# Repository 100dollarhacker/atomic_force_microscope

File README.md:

This repository holds the files for creating simple diy atomic force microscope.

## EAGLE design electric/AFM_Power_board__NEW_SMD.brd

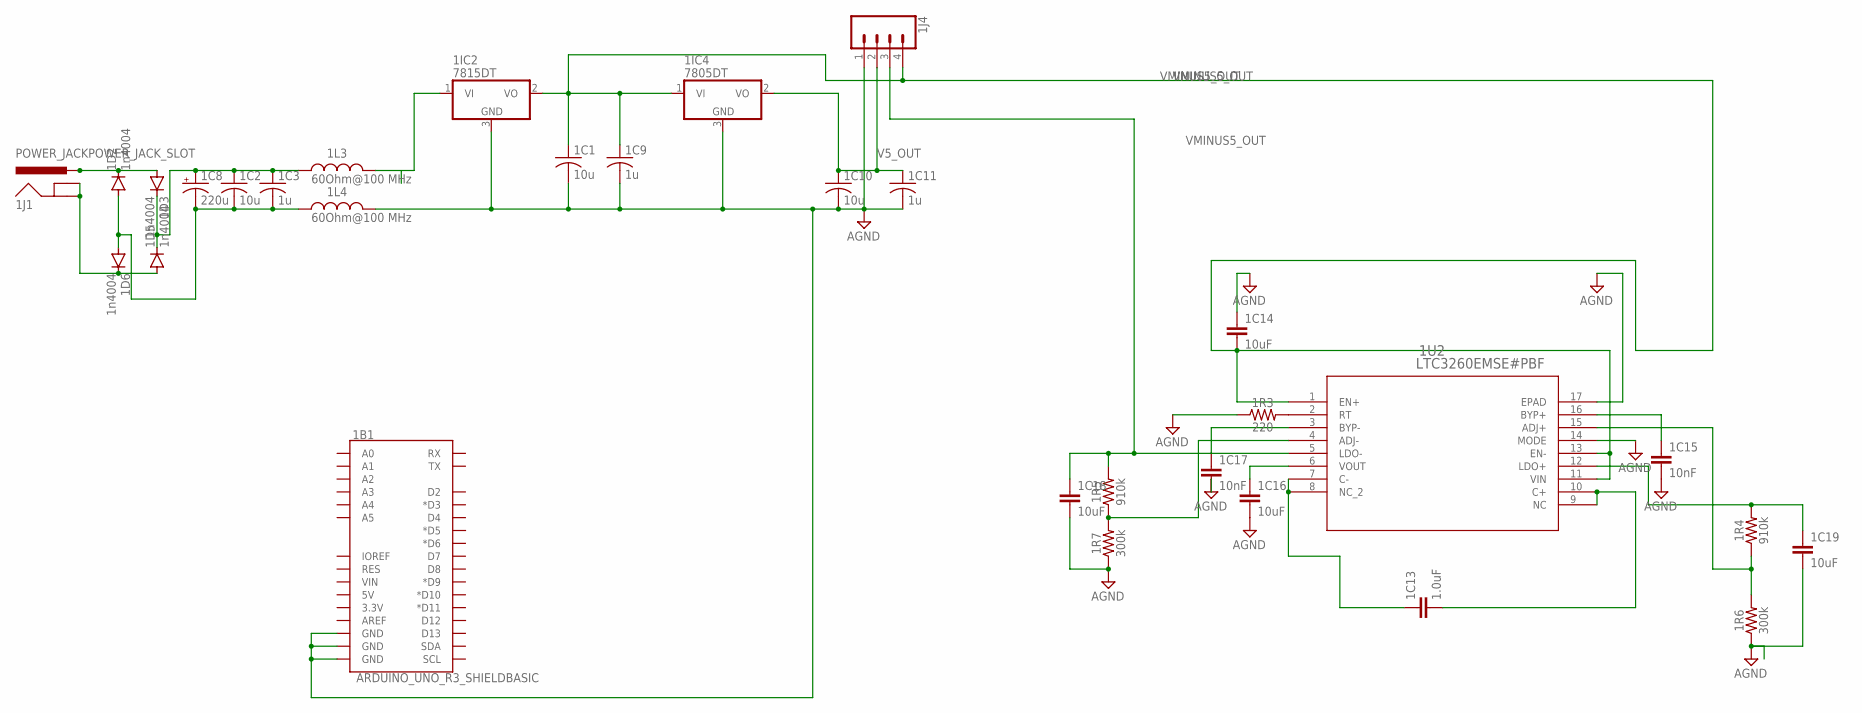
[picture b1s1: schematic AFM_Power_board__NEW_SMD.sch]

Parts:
1B1: ARDUINO_UNO_R3_SHIELDBASIC; UNO_R3_SHIELD
1C1, 1C10: 10u; C0603
1C2: 10u; C1210
1C3: 1u; C1210
1C8: 220u; 140CLH-1014
1C9, 1C11: 1u; C0603
1C13: 1.0uF; 0805
1C14, 1C16, 1C18, 1C19: 10uF; 0805
1C15, 1C17: 10nF; 0603
1D2, 1D3, 1D5, 1D6: 1n4004; SOD123
1IC2: 7815DT; TO252
1IC4: 7805DT; TO252
1J1: POWER_JACKPOWER_JACK_SLOT; POWER_JACK_PTH_SLOT
1J4: CONN_04LONGPADS; 1X04_LONGPADS
1L3, 1L4: 60Ohm@100 MHz; WE-CBF_0603_W2.2
1R3: 220; 0603
1R4, 1R5: 910k; 0603
1R6, 1R7: 300k; 0603
1U2: LTC3260EMSE#PBF; MSOP-16_MSE

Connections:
AGND: 1B1.GND@0 (GND), 1B1.GND@1 (GND), 1B1.GND@2 (GND), 1C1.2, 1C9.2, 1C10.2, 1C11.2, 1C14.1, 1C15.2, 1C16.2, 1C17.2, 1C18.2, 1C19.2, 1IC2.3 (GND), 1IC4.3 (GND), 1J4.1, 1L4.2, 1R3.1, 1R6.1, 1R7.1, 1U2.14 (MODE), 1U2.17 (EPAD)
GROUND: 1C2.2, 1C3.2, 1C8.-, 1D2.A, 1D6.A, 1L4.1
LDO+: 1C19.1, 1R4.2, 1U2.12 (LDO+)
unnamed: 1D5.A, 1D6.C, 1J1.GND, 1J1.GNDBREAK
unnamed: 1IC2.1 (VI), 1L3.2
unnamed: 1C13.1, 1U2.7 (C-), 1U2.8 (NC_2)
unnamed: 1C13.2, 1U2.9 (NC), 1U2.10 (C+)
unnamed: 1C2.1, 1C3.1, 1C8.+, 1D3.C, 1D5.C, 1L3.1
unnamed: 1C17.1, 1U2.3 (BYP-)
unnamed: 1C15.1, 1U2.16 (BYP+)
unnamed: 1C16.1, 1U2.6 (VOUT)
unnamed: 1R3.2, 1U2.2 (RT)
unnamed: 1R5.1, 1R7.2, 1U2.4 (ADJ-)
unnamed: 1R4.1, 1R6.2, 1U2.15 (ADJ+)
POWERP: 1D2.C, 1D3.A, 1J1.PWR
V5_OUT: 1C10.1, 1C11.1, 1IC4.2 (VO), 1J4.2
V15+: 1C1.1, 1C9.1, 1C14.2, 1IC2.2 (VO), 1IC4.1 (VI), 1J4.4, 1U2.1 (EN+), 1U2.11 (VIN), 1U2.13 (EN-)
VMINUS5_OUT: 1C18.1, 1J4.3, 1R5.2, 1U2.5 (LDO-)

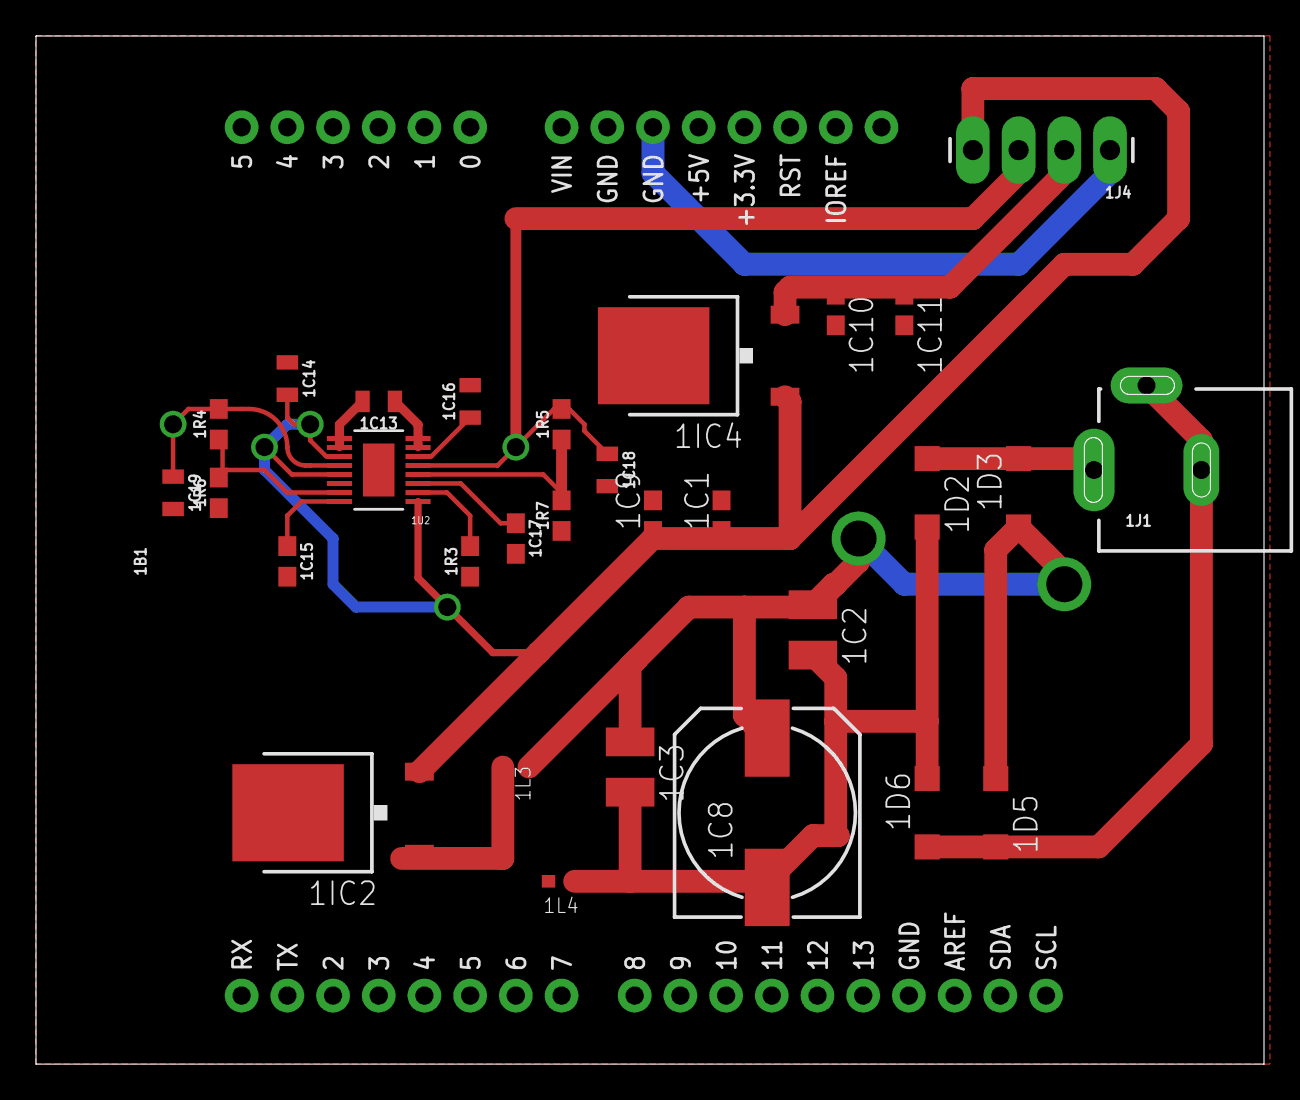
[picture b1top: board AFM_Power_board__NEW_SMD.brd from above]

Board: 2 copper layers, 68.2 x 57.1 mm, 31 parts (0 on the bottom side), 18 nets.

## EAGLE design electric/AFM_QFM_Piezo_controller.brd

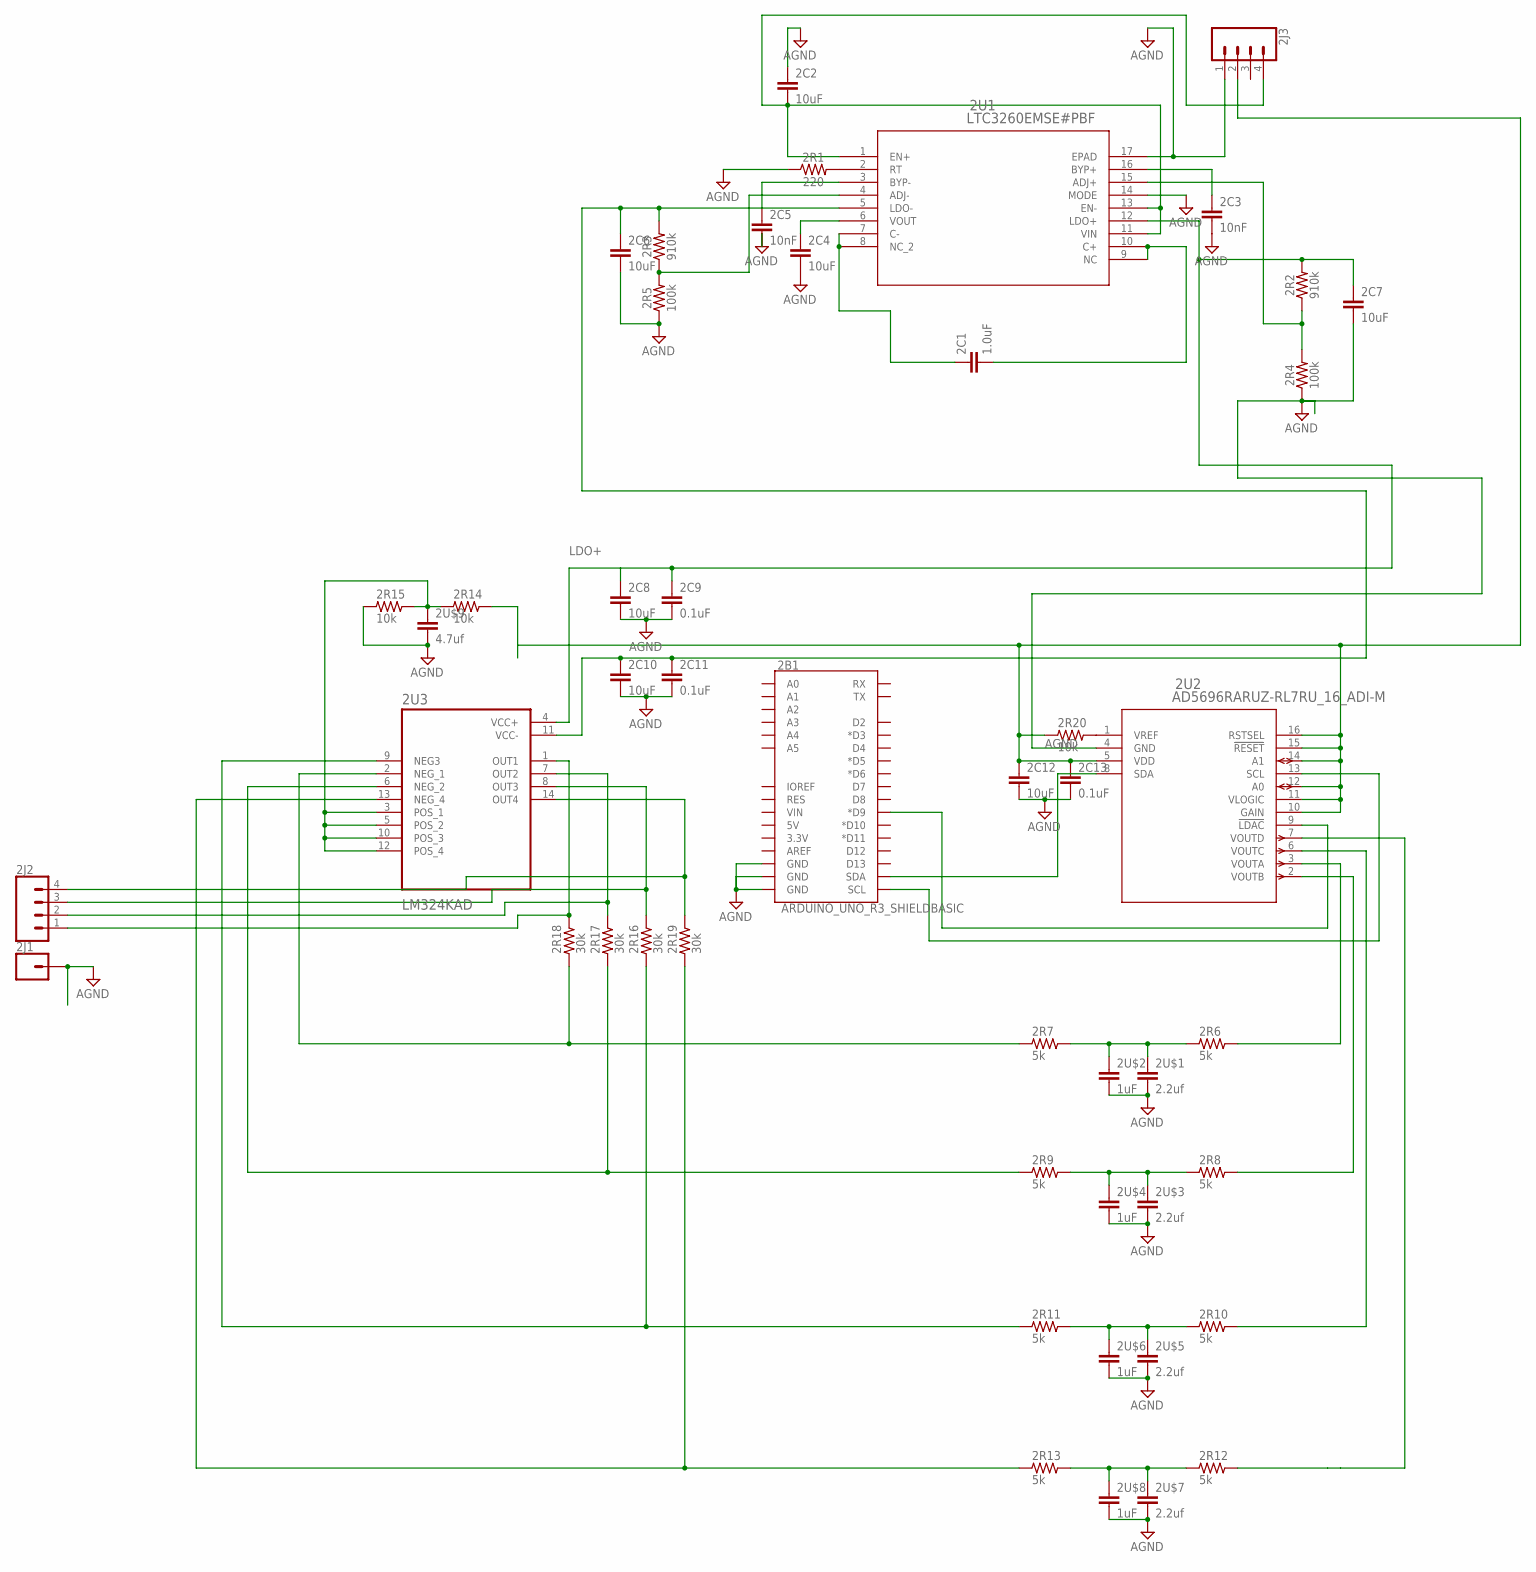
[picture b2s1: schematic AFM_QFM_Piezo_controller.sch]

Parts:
2B1: ARDUINO_UNO_R3_SHIELDBASIC; UNO_R3_SHIELD
2C1: 1.0uF; 0805
2C2, 2C4, 2C6, 2C7, 2C8, 2C10, 2C12: 10uF; 0805
2C3, 2C5: 10nF; 0603
2C9, 2C11, 2C13: 0.1uF; C0805
2J1: CONN_01PTH_LONGPAD; 1X01_LONGPAD
2J2, 2J3: CONN_04LONGPADS; 1X04_LONGPADS
2R1: 220; 0603
2R2, 2R3: 910k; 0603
2R4, 2R5: 100k; 0603
2R6, 2R7, 2R8, 2R9, 2R10, 2R11, 2R12, 2R13: 5k; RC-MASTER-SMD_R0603MP
2R14, 2R15, 2R20: 10k; RC-MASTER-SMD_R0603MP
2R16, 2R17, 2R18, 2R19: 30k; RC-MASTER-SMD_R0603MP
2U1: LTC3260EMSE#PBF; MSOP-16_MSE
2U2: AD5696RARUZ-RL7RU_16_ADI-M; RU_16_ADI-M
2U3: LM324KAD; SOIC127P600X175-14N
2U$1, 2U$3, 2U$5, 2U$7: 2.2uf; RESC0603_M
2U$2, 2U$4, 2U$6, 2U$8: 1uF; RESC0603_M
2U$9: 4.7uf; RESC0603_M

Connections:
AGND: 2B1.GND@0 (GND), 2B1.GND@1 (GND), 2B1.GND@2 (GND), 2C2.1, 2C3.2, 2C4.2, 2C5.2, 2C6.2, 2C7.2, 2C8.2, 2C9.2, 2C10.2, 2C11.2, 2C12.2, 2C13.2, 2J1.1, 2J3.1, 2R1.1, 2R4.1, 2R5.1, 2R15.1, 2U1.14 (MODE), 2U1.17 (EPAD), 2U2.4 (GND), 2U$1.2, 2U$2.2, 2U$3.2, 2U$4.2, 2U$5.2, 2U$6.2, 2U$7.2, 2U$8.2, 2U$9.2
LDAC: 2B1.D9 (*D9), 2U2.9 (!LDAC)
LDO+: 2C7.1, 2C8.1, 2C9.1, 2R2.2, 2U1.12 (LDO+), 2U3.4 (VCC+)
LDO-: 2C6.1, 2C10.1, 2C11.1, 2R3.2, 2U1.5 (LDO-), 2U3.11 (VCC-)
unnamed: 2C5.1, 2U1.3 (BYP-)
unnamed: 2R1.2, 2U1.2 (RT)
unnamed: 2C1.1, 2U1.7 (C-), 2U1.8 (NC_2)
unnamed: 2C1.2, 2U1.9 (NC), 2U1.10 (C+)
unnamed: 2C3.1, 2U1.16 (BYP+)
unnamed: 2C4.1, 2U1.6 (VOUT)
unnamed: 2R3.1, 2R5.2, 2U1.4 (ADJ-)
unnamed: 2R6.1, 2R7.2, 2U$1.1, 2U$2.1
unnamed: 2R2.1, 2R4.2, 2U1.15 (ADJ+)
unnamed: 2R7.1, 2R18.1, 2U3.2 (NEG_1)
unnamed: 2R8.1, 2R9.2, 2U$3.1, 2U$4.1
unnamed: 2R9.1, 2R17.1, 2U3.6 (NEG_2)
unnamed: 2R10.1, 2R11.2, 2U$5.1, 2U$6.1
unnamed: 2R11.1, 2R16.1, 2U3.9 (NEG3)
unnamed: 2R12.1, 2R13.2, 2U$7.1, 2U$8.1
unnamed: 2R13.1, 2R19.1, 2U3.13 (NEG_4)
unnamed: 2R20.2, 2U2.1 (VREF)
P_OUT1: 2J2.1, 2R18.2, 2U3.1 (OUT1)
P_OUT2: 2J2.2, 2R17.2, 2U3.7 (OUT2)
P_OUT3: 2J2.3, 2R16.2, 2U3.8 (OUT3)
P_OUT4: 2J2.4, 2R19.2, 2U3.14 (OUT4)
SCL: 2B1.SCL, 2U2.13 (SCL)
SDA: 2B1.SDA, 2U2.8 (SDA)
V15+: 2C2.2, 2J3.4, 2U1.1 (EN+), 2U1.11 (VIN), 2U1.13 (EN-)
VDD: 2C12.1, 2C13.1, 2J3.2, 2R14.2, 2R20.1, 2U2.5 (VDD), 2U2.10 (GAIN), 2U2.11 (VLOGIC), 2U2.12 (A0), 2U2.14 (A1), 2U2.15 (!RESET), 2U2.16 (RSTSEL)
VOUTA: 2R6.2, 2U2.3 (VOUTA)
VOUTB: 2R8.2, 2U2.2 (VOUTB)
VOUTC: 2R10.2, 2U2.6 (VOUTC)
VOUTD: 2R12.2, 2U2.7 (VOUTD)
V_REF: 2R14.1, 2R15.2, 2U3.3 (POS_1), 2U3.5 (POS_2), 2U3.10 (POS_3), 2U3.12 (POS_4), 2U$9.1

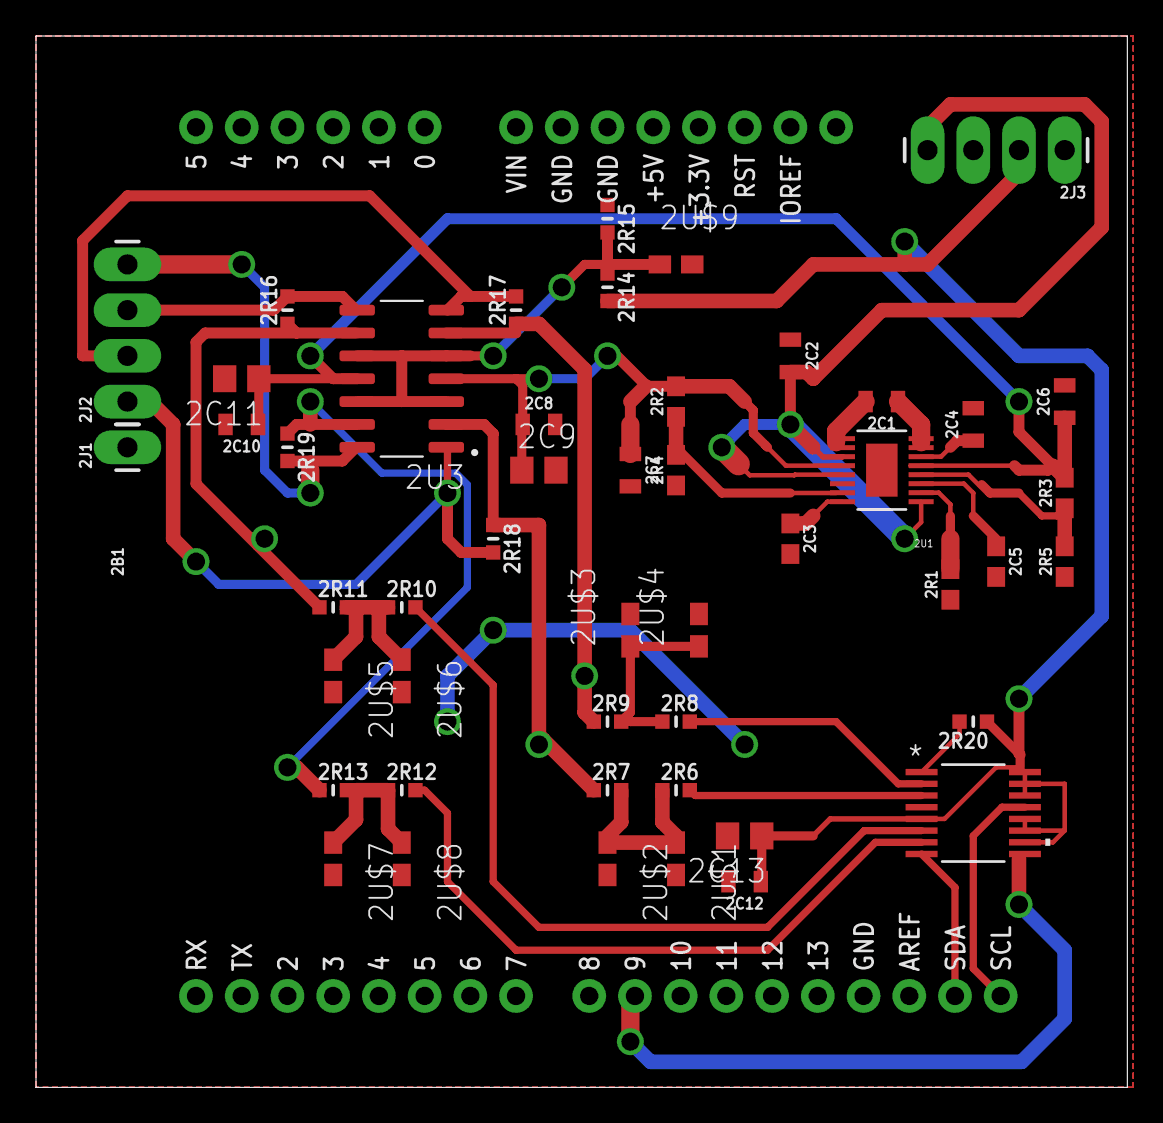
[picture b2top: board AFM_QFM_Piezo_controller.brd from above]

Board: 2 copper layers, 60.6 x 58.4 mm, 49 parts (0 on the bottom side), 34 nets.

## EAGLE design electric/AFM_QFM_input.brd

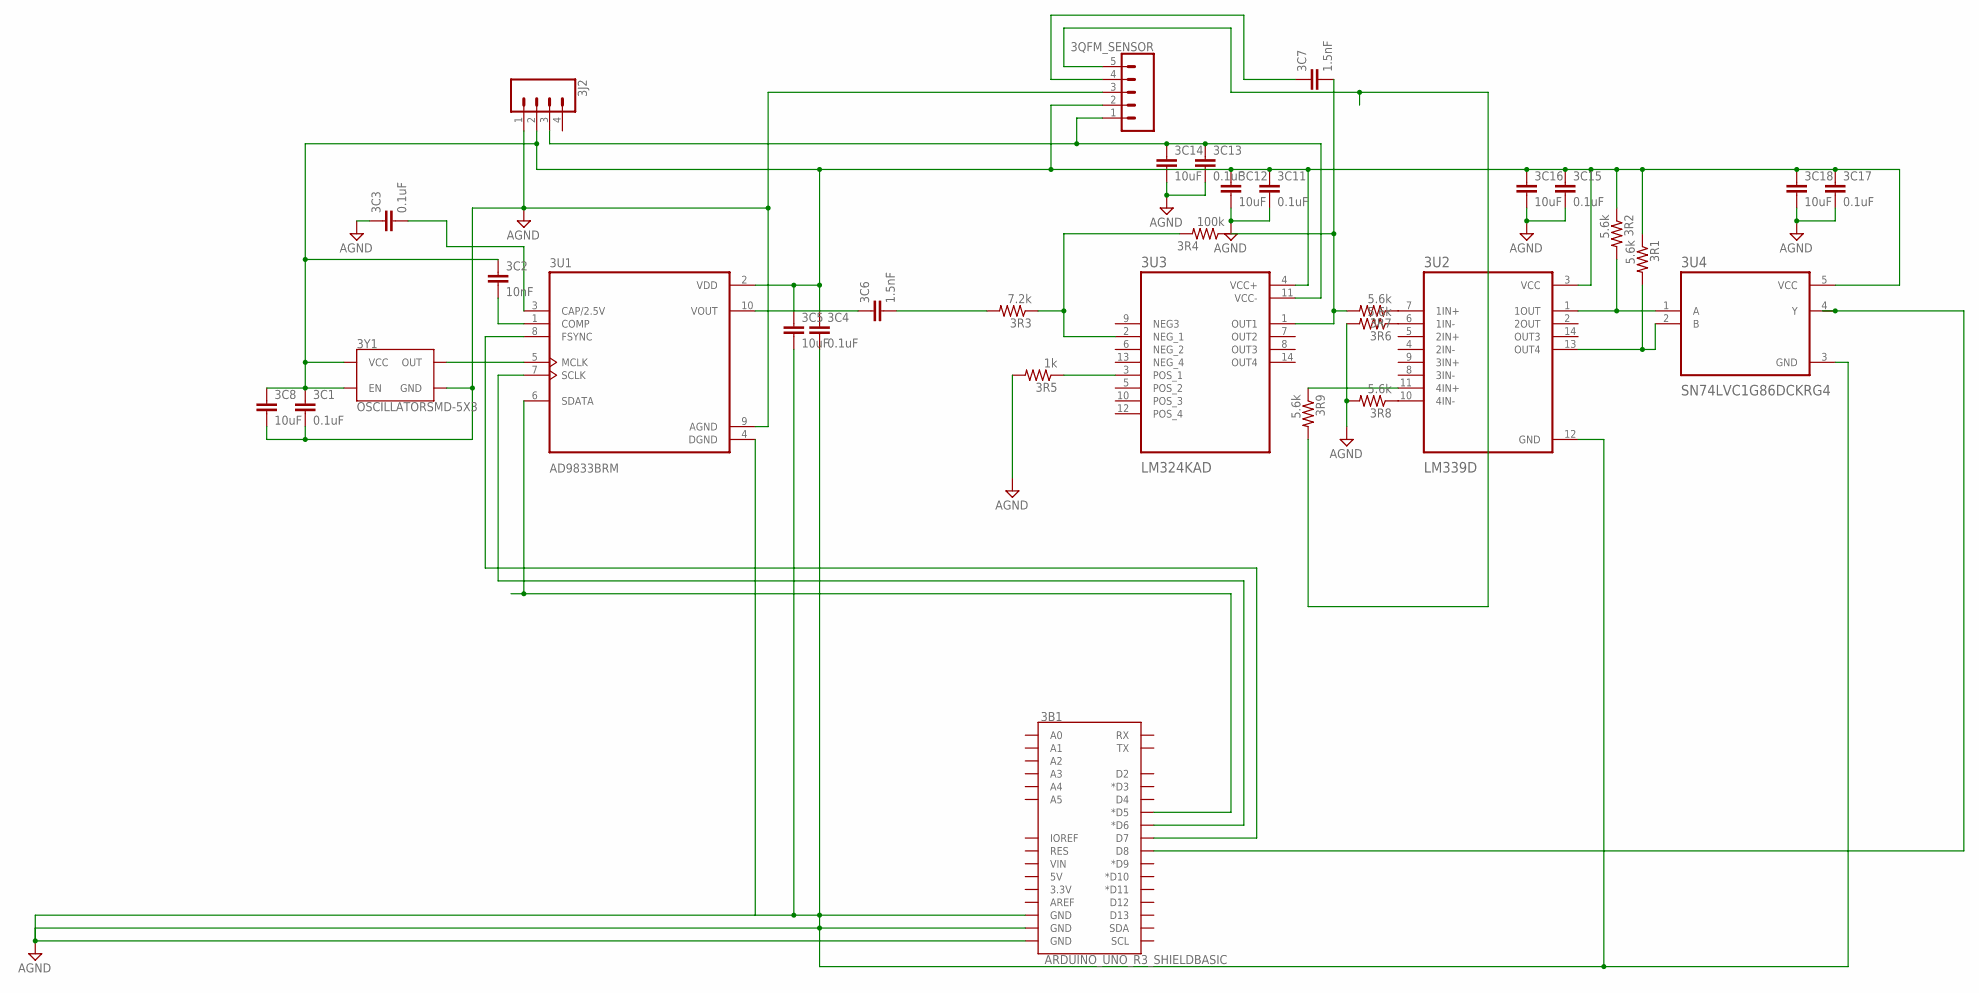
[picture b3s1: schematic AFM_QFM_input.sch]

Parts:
3B1: ARDUINO_UNO_R3_SHIELDBASIC; UNO_R3_SHIELD
3C1, 3C3, 3C4, 3C11, 3C13, 3C15, 3C17: 0.1uF; 0603
3C2: 10nF; 0603
3C5, 3C8, 3C12, 3C14, 3C16, 3C18: 10uF; 0805
3C6, 3C7: 1.5nF; C0603
3J2: CONN_04LONGPADS; 1X04_LONGPADS
3QFM_SENSOR: CONN_05PTH_LONGPADS; 1X05_LONGPADS
3R1, 3R2, 3R6, 3R7, 3R8, 3R9: 5.6k; R0603
3R3: 7.2k; R0603
3R4: 100k; R0603
3R5: 1k; R0603
3U1: AD9833BRM; SOP50P490X110-10N
3U2: LM339D; SOIC127P600X175-14N
3U3: LM324KAD; SOIC127P600X175-14N
3U4: SN74LVC1G86DCKRG4; SOT65P210X110-5N
3Y1: OSCILLATORSMD-5X3; OSCILLATOR-SMD-5X3.2

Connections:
AGND: 3B1.GND@0 (GND), 3B1.GND@1 (GND), 3B1.GND@2 (GND), 3C1.2, 3C3.1, 3C4.2, 3C5.2, 3C8.2, 3C11.2, 3C12.2, 3C13.2, 3C14.2, 3C15.2, 3C16.2, 3C17.2, 3C18.2, 3J2.1, 3QFM_SENSOR.3, 3R5.2, 3R6.2, 3R8.2, 3U1.4 (DGND), 3U1.9 (AGND), 3U2.12 (GND), 3U4.3 (GND), 3Y1.2 (GND)
unnamed: 3B1.D7, 3U1.8 (FSYNC)
unnamed: 3U1.5 (MCLK), 3Y1.3 (OUT)
unnamed: 3B1.D6 (*D6), 3U1.7 (SCLK)
unnamed: 3B1.D5 (*D5), 3U1.6 (SDATA)
unnamed: 3C2.2, 3U1.1 (COMP)
unnamed: 3C6.1, 3U1.10 (VOUT)
unnamed: 3C3.2, 3U1.3 (CAP/2.5V)
unnamed: 3C6.2, 3R3.2
unnamed: 3R3.1, 3R4.2, 3U3.2 (NEG_1)
unnamed: 3C7.1, 3QFM_SENSOR.4
unnamed: 3C7.2, 3R4.1, 3R7.2, 3U3.1 (OUT1)
unnamed: 3R5.1, 3U3.3 (POS_1)
unnamed: 3R6.1, 3U2.6 (1IN-)
unnamed: 3R7.1, 3U2.7 (1IN+)
unnamed: 3R2.2, 3U2.1 (1OUT), 3U4.1 (A)
unnamed: 3R8.1, 3U2.10 (4IN-)
unnamed: 3R9.1, 3U2.11 (4IN+)
unnamed: 3QFM_SENSOR.5, 3R9.2
unnamed: 3R1.2, 3U2.13 (OUT4), 3U4.2 (B)
unnamed: 3B1.D8, 3U4.4 (Y)
VCC: 3C13.1, 3C14.1, 3J2.3, 3QFM_SENSOR.1, 3U3.11 (VCC-)
VDD3: 3C1.1, 3C2.1, 3C4.1, 3C5.1, 3C8.1, 3C11.1, 3C12.1, 3C15.1, 3C16.1, 3C17.1, 3C18.1, 3J2.2, 3QFM_SENSOR.2, 3R1.1, 3R2.1, 3U1.2 (VDD), 3U2.3 (VCC), 3U3.4 (VCC+), 3U4.5 (VCC), 3Y1.1 (EN), 3Y1.4 (VCC)

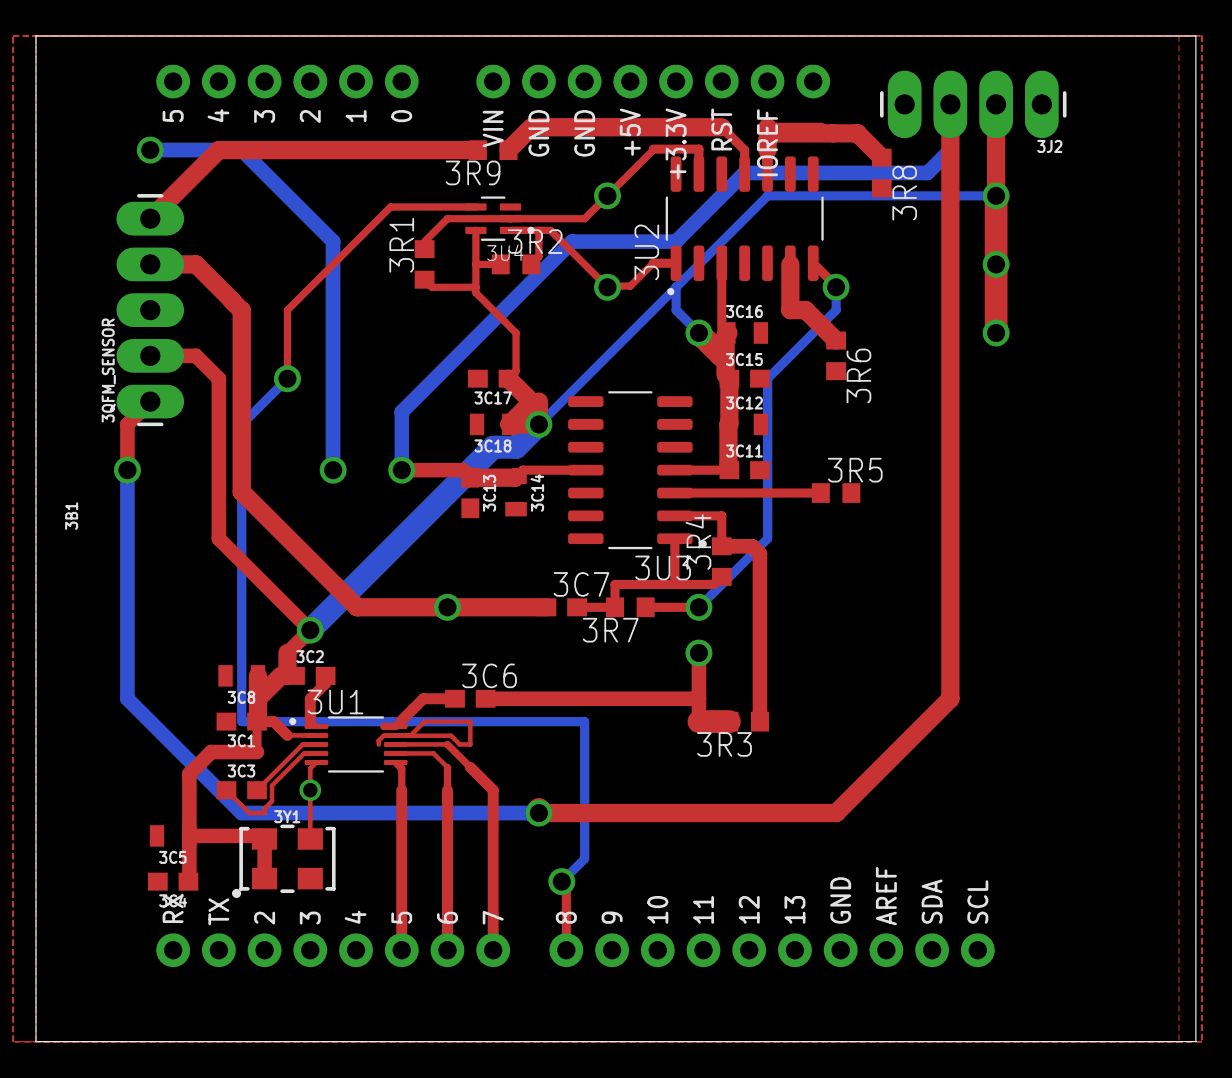
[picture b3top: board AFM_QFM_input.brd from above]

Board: 2 copper layers, 64.4 x 55.9 mm, 33 parts (0 on the bottom side), 23 nets.

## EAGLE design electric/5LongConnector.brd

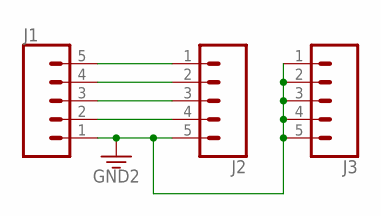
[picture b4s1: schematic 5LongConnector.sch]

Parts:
J1, J2, J3: CONN_05PTH_LONGPADS; 1X05_LONGPADS

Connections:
3.3V: J1.1, J2.5, J3.1, J3.2, J3.3, J3.4, J3.5
unnamed: J1.5, J2.1
unnamed: J1.4, J2.2
unnamed: J1.3, J2.3
unnamed: J1.2, J2.4

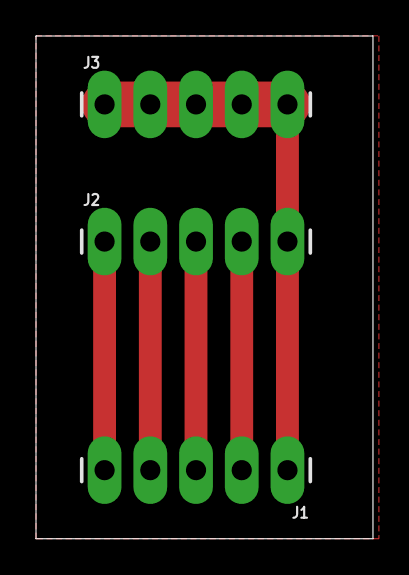
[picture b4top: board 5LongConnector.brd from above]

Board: 2 copper layers, 18.7 x 27.9 mm, 3 parts (0 on the bottom side), 5 nets.

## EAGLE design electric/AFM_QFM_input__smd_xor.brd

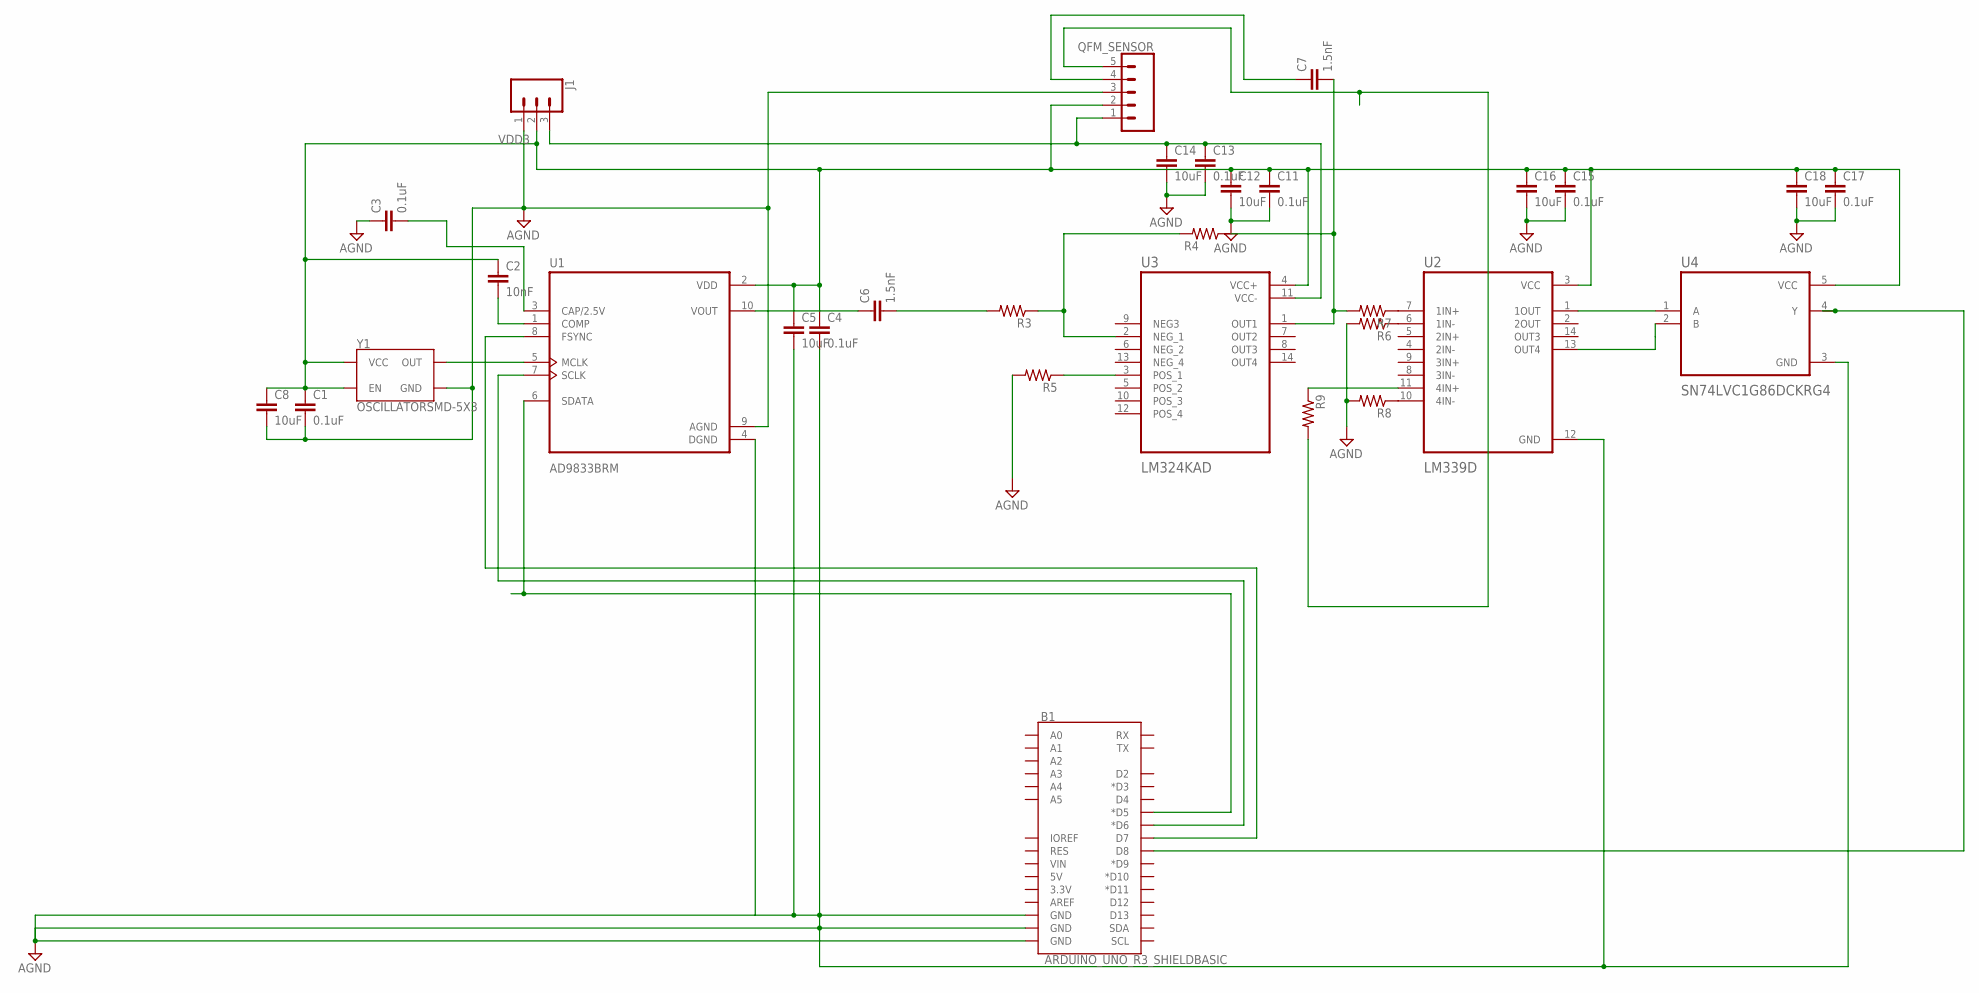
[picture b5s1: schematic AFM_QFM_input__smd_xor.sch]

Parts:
B1: ARDUINO_UNO_R3_SHIELDBASIC; UNO_R3_SHIELD
C1, C3, C4, C11, C13, C15, C17: 0.1uF; 0603
C2: 10nF; 0603
C5, C8, C12, C14, C16, C18: 10uF; 0805
C6, C7: 1.5nF; C0603
J1: CONN_03LONGPADS; 1X03_LONGPADS
QFM_SENSOR: CONN_05PTH_LONGPADS; 1X05_LONGPADS
R3, R4, R5, R6, R7, R8, R9: R-US_R0603; R0603
U1: AD9833BRM; SOP50P490X110-10N
U2: LM339D; SOIC127P600X175-14N
U3: LM324KAD; SOIC127P600X175-14N
U4: SN74LVC1G86DCKRG4; SOT65P210X110-5N
Y1: OSCILLATORSMD-5X3; OSCILLATOR-SMD-5X3.2

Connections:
AGND: B1.GND@0 (GND), B1.GND@1 (GND), B1.GND@2 (GND), C1.2, C3.1, C4.2, C5.2, C8.2, C11.2, C12.2, C13.2, C14.2, C15.2, C16.2, C17.2, C18.2, J1.1, QFM_SENSOR.3, R5.2, R6.2, R8.2, U1.4 (DGND), U1.9 (AGND), U2.12 (GND), U4.3 (GND), Y1.2 (GND)
unnamed: B1.D7, U1.8 (FSYNC)
unnamed: U1.5 (MCLK), Y1.3 (OUT)
unnamed: B1.D6 (*D6), U1.7 (SCLK)
unnamed: B1.D5 (*D5), U1.6 (SDATA)
unnamed: C2.2, U1.1 (COMP)
unnamed: C6.1, U1.10 (VOUT)
unnamed: C3.2, U1.3 (CAP/2.5V)
unnamed: C6.2, R3.2
unnamed: R3.1, R4.2, U3.2 (NEG_1)
unnamed: C7.1, QFM_SENSOR.4
unnamed: C7.2, R4.1, R7.2, U3.1 (OUT1)
unnamed: R5.1, U3.3 (POS_1)
unnamed: R6.1, U2.6 (1IN-)
unnamed: R7.1, U2.7 (1IN+)
unnamed: U2.1 (1OUT), U4.1 (A)
unnamed: R8.1, U2.10 (4IN-)
unnamed: R9.1, U2.11 (4IN+)
unnamed: QFM_SENSOR.5, R9.2
unnamed: U2.13 (OUT4), U4.2 (B)
unnamed: B1.D8, U4.4 (Y)
VCC: C13.1, C14.1, J1.3, QFM_SENSOR.1, U3.11 (VCC-)
VDD3: C1.1, C2.1, C4.1, C5.1, C8.1, C11.1, C12.1, C15.1, C16.1, C17.1, C18.1, J1.2, QFM_SENSOR.2, U1.2 (VDD), U2.3 (VCC), U3.4 (VCC+), U4.5 (VCC), Y1.1 (EN), Y1.4 (VCC)

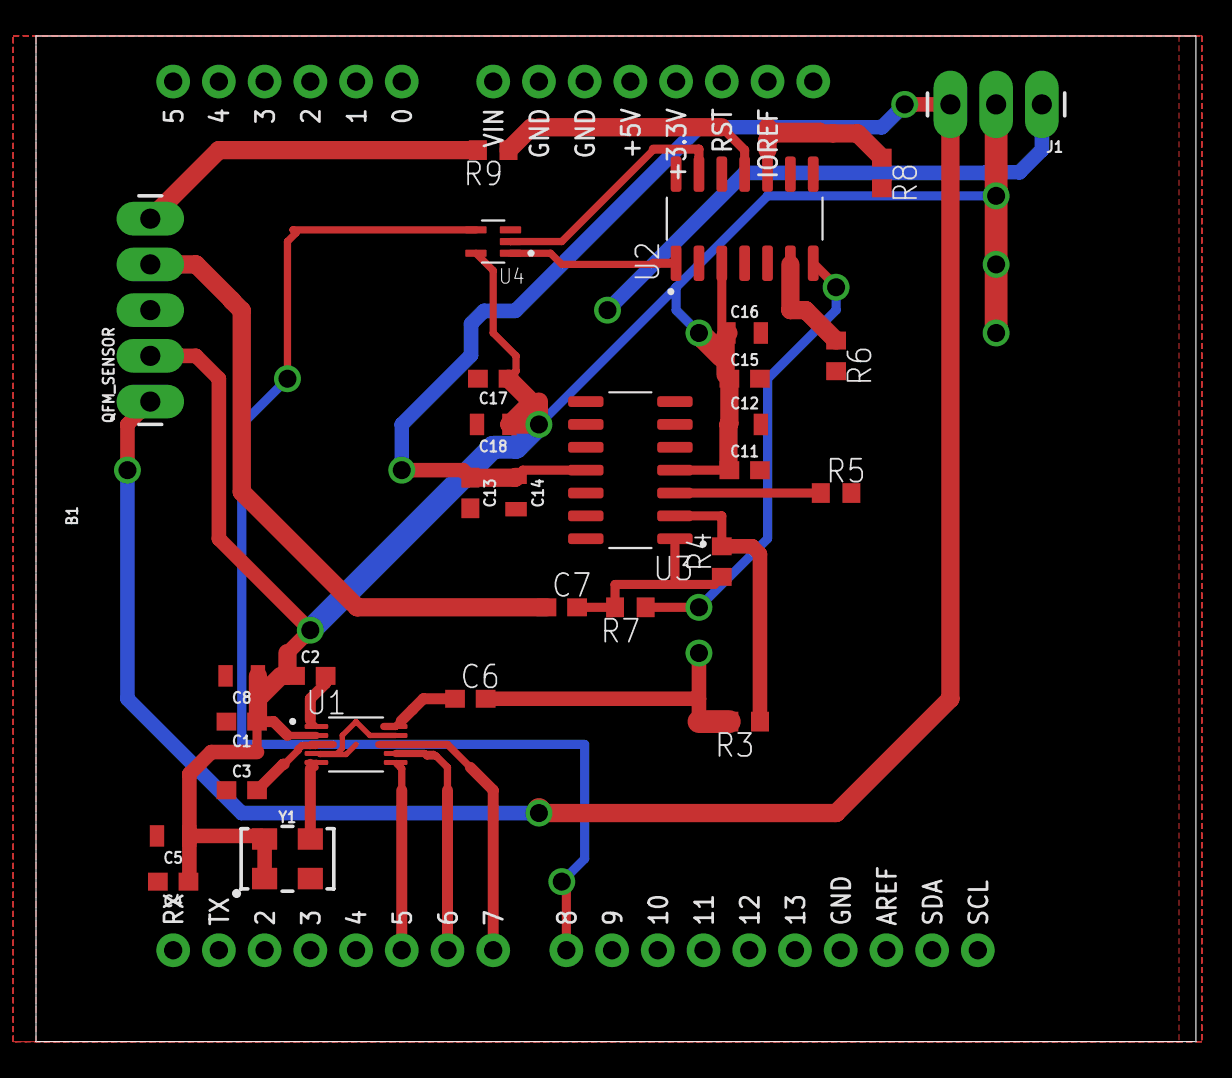
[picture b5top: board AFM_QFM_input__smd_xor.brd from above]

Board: 2 copper layers, 64.4 x 55.9 mm, 31 parts (0 on the bottom side), 23 nets.

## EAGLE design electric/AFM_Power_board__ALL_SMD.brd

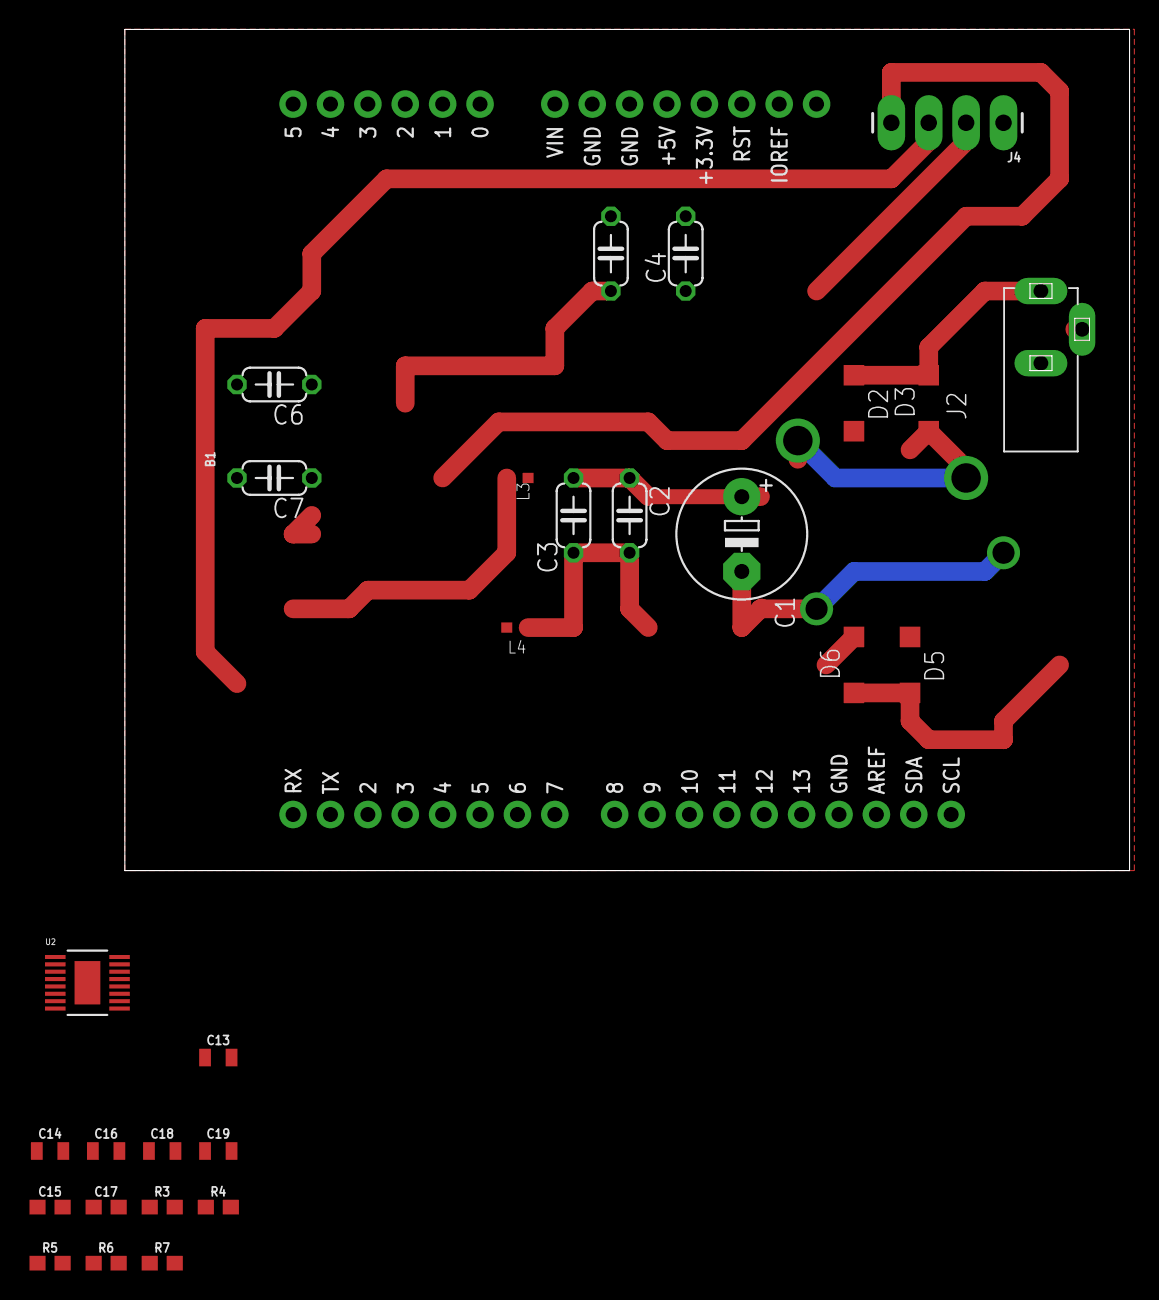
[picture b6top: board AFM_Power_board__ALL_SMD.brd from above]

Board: 2 copper layers, 68.2 x 57.1 mm, 29 parts (0 on the bottom side), 16 nets.

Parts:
B1: ARDUINO_UNO_R3_SHIELDBASIC; UNO_R3_SHIELD
C1: 220uF; E5-8,5
C2, C4, C6: 10uF; C050-024X044
C3, C5, C7: 1uF; C050-024X044
C13: 1.0uF; 0805
C14, C16, C18, C19: 10uF; 0805
C15, C17: 10nF; 0603
D2, D3, D5, D6: 1n4004; SOD123
J2: 694103303002
J4: 1X04_LONGPADS
L3, L4: 60Ohm@100 MHz; WE-CBF_0603_W2.2
R3: 220; 0603
R4, R5: 100k; 0603
R6, R7: 300k; 0603
U2: LTC3260EMSE#PBF; MSOP-16_MSE

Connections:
AGND: B1.GND@0, B1.GND@1, C4.2, C5.2, C6.2, C7.2, C14.1, C15.2, C16.2, C17.2, C18.2, C19.2, J4.1, L4.2, R3.1, R6.1, R7.1, U2.14, U2.17
LDO+: C19.1, R4.2, U2.12
LDO-: C18.1, R5.2, U2.5
unnamed: C13.1, U2.7, U2.8
unnamed: C13.2, U2.9, U2.10
unnamed: D5.A, D6.C
unnamed: C17.1, U2.3
unnamed: C15.1, U2.16
unnamed: C16.1, U2.6
unnamed: R3.2, U2.2
unnamed: R5.1, R7.2, U2.4
unnamed: R4.1, R6.2, U2.15
POWERP: D2.C, D3.A, J2.1
S$3: C1.+, C2.1, C3.1
S$4: C2.2, C3.2, L4.1
V15+: U2.1, U2.11, U2.13

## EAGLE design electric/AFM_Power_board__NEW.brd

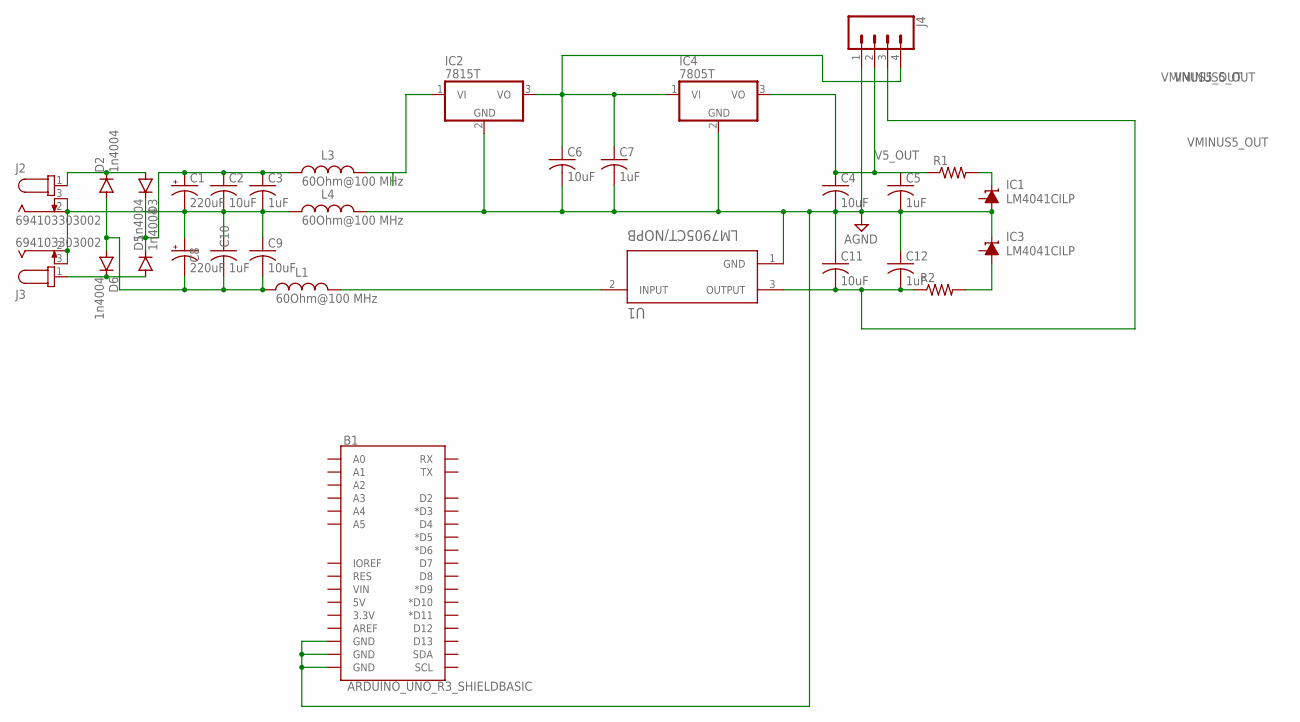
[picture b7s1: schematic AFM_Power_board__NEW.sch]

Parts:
B1: ARDUINO_UNO_R3_SHIELDBASIC; UNO_R3_SHIELD
C1, C8: 220uF; E5-8,5
C2, C4, C6, C9, C11: 10uF; C050-024X044
C3, C5, C7, C10, C12: 1uF; C050-024X044
D2, D3, D5, D6: 1n4004; SOD123
IC1, IC3: LM4041CILP; LP_O-PBCY-W3
IC2: 7815T; TO220H
IC4: 7805T; TO220H
J2, J3: 694103303002
J4: CONN_04LONGPADS; 1X04_LONGPADS
L1, L3, L4: 60Ohm@100 MHz; WE-CBF_0603_W2.2
R1, R2: R-US_0204/5; 0204/5
U1: LM7905CT/NOPB; TO254P1016X4575X1955-3

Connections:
AGND: B1.GND@0 (GND), B1.GND@1 (GND), B1.GND@2 (GND), C4.2, C5.2, C6.2, C7.2, C11.1, C12.1, IC1.3 (A), IC2.2 (GND), IC3.2 (C), IC4.2 (GND), J4.1, L4.2, U1.1 (GND)
GROUND: C1.-, C2.2, C3.2, C8.+, C9.1, C10.1, J2.2, J2.3, J3.2, J3.3, L4.1
unnamed: C6.1, C7.1, IC2.3 (VO), IC4.1 (VI), J4.4
unnamed: L1.2, U1.2 (INPUT)
unnamed: IC1.2 (C), R1.2
unnamed: IC2.1 (VI), L3.2
unnamed: IC3.3 (A), R2.2
unnamed: D5.A, D6.C, J3.1
unnamed: C8.-, C9.2, C10.2, D2.A, D6.A, L1.1
unnamed: C1.+, C2.1, C3.1, D3.C, D5.C, L3.1
POWERP: D2.C, D3.A, J2.1
V5_OUT: C4.1, C5.1, IC4.3 (VO), J4.2, R1.1
VMINUS5_OUT: C11.2, C12.2, J4.3, R2.1, U1.3 (OUTPUT)

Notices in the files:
parts and their libraries:
SparkFun-Connectors: Licensing: Creative Commons ShareAlike 4.0 International - https://creativecommons.org/licenses/by-sa/4.0
Wurth_EMC Components_WE-CBF: Copyright: Würth Elektronik
COPYRIGHT: Copyright (C) 2024 Ultra Librarian. All rights reserved.
